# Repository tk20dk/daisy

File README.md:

# daisy
Sx1262 / Sx1268 usb gateway

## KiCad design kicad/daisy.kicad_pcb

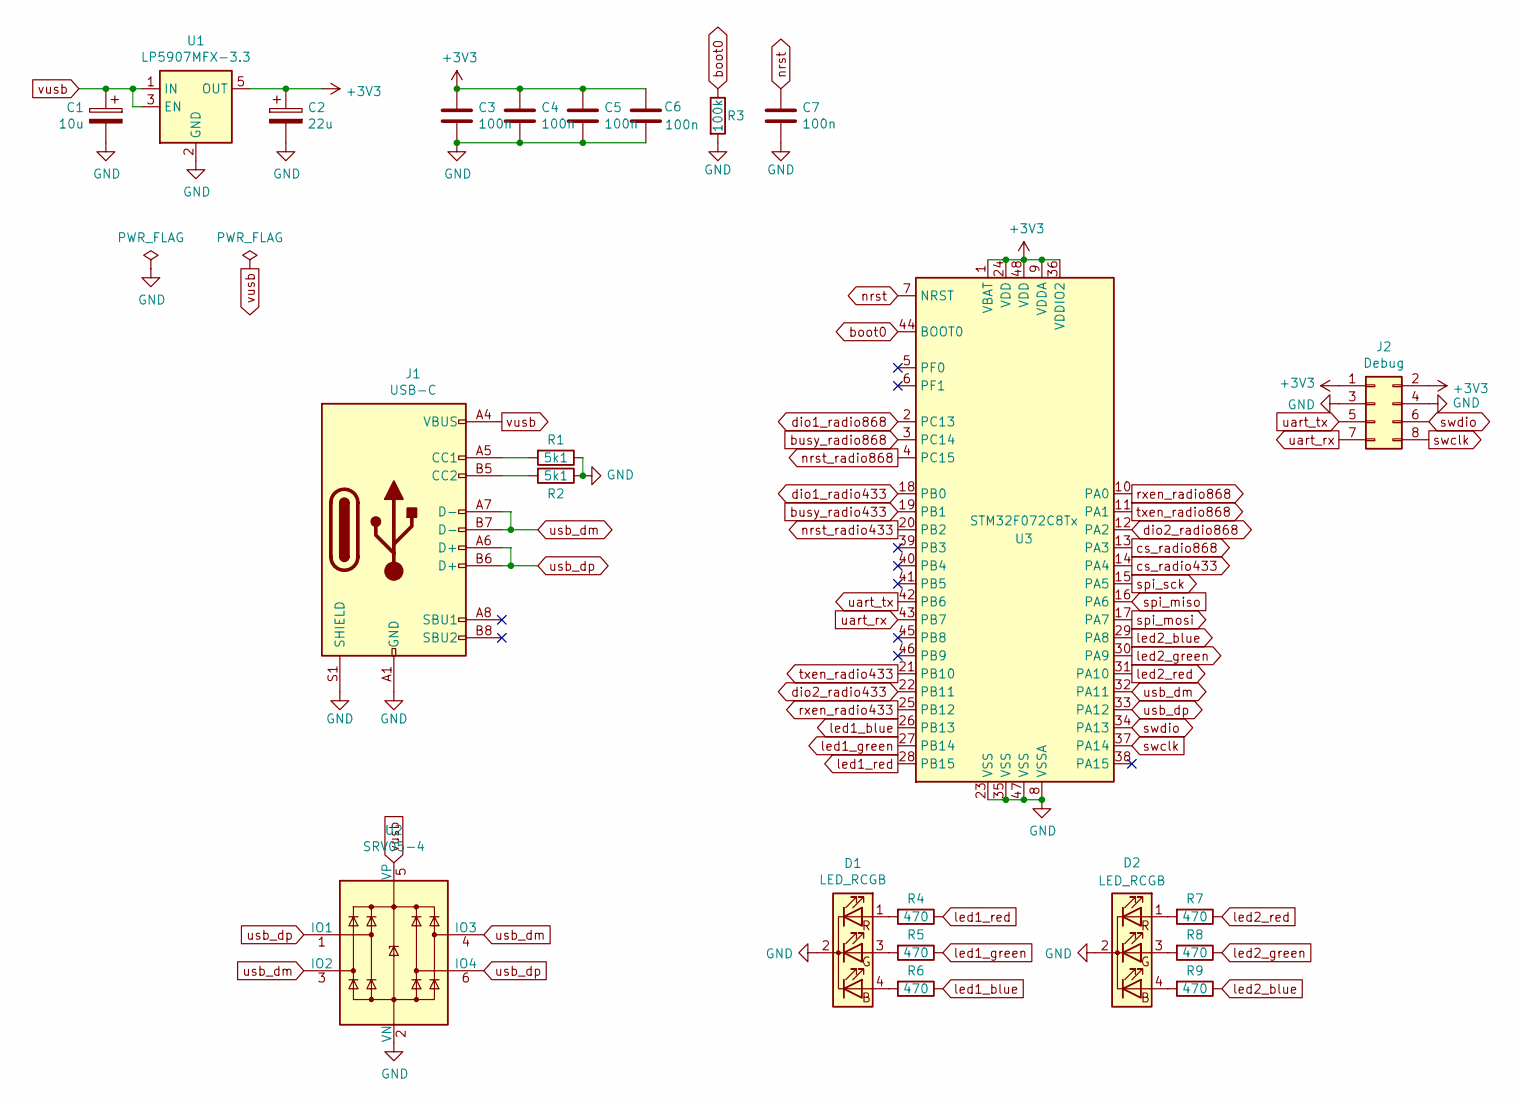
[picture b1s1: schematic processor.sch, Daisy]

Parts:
C1: 10u; CP_EIA-3528-12_Kemet-T
C2: 22u; CP_EIA-3528-12_Kemet-T
C3, C4, C5, C6, C7: 100n; C_0603_1608Metric
D1, D2: LED_RCGB; LED_D5.0mm-4
J1: USB-C; USB_C_Receptacle_HRO_TYPE-C-31-M-12
J2: Debug; PinHeader_2x04_P2.54mm_Vertical
R1, R2: 5k1; R_0603_1608Metric
R3: 100k; R_0603_1608Metric
R4, R5, R6, R7, R8, R9: 470; R_0603_1608Metric
U1: LP5907MFX-3.3; SOT-23-5
U2: SRV05-4; SOT-23-6
U3: STM32F072C8Tx; LQFP-48_7x7mm_P0.5mm

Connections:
GND: C1.2, C2.2, C3.2, C4.2, C5.2, C6.2, C7.2, D1.2 (K), D2.2 (K), J1.A1 (GND), J1.A12 (GND), J1.B1 (GND), J1.B12 (GND), J1.S1 (SHIELD), J2.3, J2.4, R1.1, R2.1, R3.2, U1.2 (GND), U2.2 (VN), U3.8 (VSSA), U3.23 (VSS), U3.35 (VSS), U3.47 (VSS); also elsewhere on the board
unnamed: D1.1 (RA), R4.2
unnamed: D1.3 (GA), R5.2
unnamed: D1.4 (BA), R6.2
unnamed: D2.1 (RA), R7.2
unnamed: D2.3 (GA), R8.2
unnamed: D2.4 (BA), R9.2
unnamed: J1.A5 (CC1), R1.2
unnamed: J1.B5 (CC2), R2.2
boot0: R3.1, U3.44 (BOOT0)
busy_radio433: U3.19 (PB1); also elsewhere on the board
busy_radio868: U3.3 (PC14); also elsewhere on the board
cs_radio433: U3.14 (PA4); also elsewhere on the board
cs_radio868: U3.13 (PA3); also elsewhere on the board
dio1_radio433: U3.18 (PB0); also elsewhere on the board
dio1_radio868: U3.2 (PC13); also elsewhere on the board
dio2_radio433: U3.22 (PB11); also elsewhere on the board
dio2_radio868: U3.12 (PA2); also elsewhere on the board
led1_blue: R6.1, U3.26 (PB13)
led1_green: R5.1, U3.27 (PB14)
led1_red: R4.1, U3.28 (PB15)
led2_blue: R9.1, U3.29 (PA8)
led2_green: R8.1, U3.30 (PA9)
led2_red: R7.1, U3.31 (PA10)
nrst: C7.1, U3.7 (NRST)
nrst_radio433: U3.20 (PB2); also elsewhere on the board
nrst_radio868: U3.4 (PC15); also elsewhere on the board
rxen_radio433: U3.25 (PB12); also elsewhere on the board
rxen_radio868: U3.10 (PA0); also elsewhere on the board
spi_miso: U3.16 (PA6); also elsewhere on the board
spi_mosi: U3.17 (PA7); also elsewhere on the board
spi_sck: U3.15 (PA5); also elsewhere on the board
swclk: J2.8, U3.37 (PA14)
swdio: J2.6, U3.34 (PA13)
txen_radio433: U3.21 (PB10); also elsewhere on the board
txen_radio868: U3.11 (PA1); also elsewhere on the board
uart_rx: J2.7, U3.43 (PB7)
uart_tx: J2.5, U3.42 (PB6)
usb_dm: J1.A7 (D-), J1.B7 (D-), U2.3 (IO2), U2.4 (IO3), U3.32 (PA11)
usb_dp: J1.A6 (D+), J1.B6 (D+), U2.1 (IO1), U2.6 (IO4), U3.33 (PA12)
vusb: C1.1, J1.A4 (VBUS), J1.A9 (VBUS), J1.B4 (VBUS), J1.B9 (VBUS), U1.1 (IN), U1.3 (EN), U2.5 (VP)

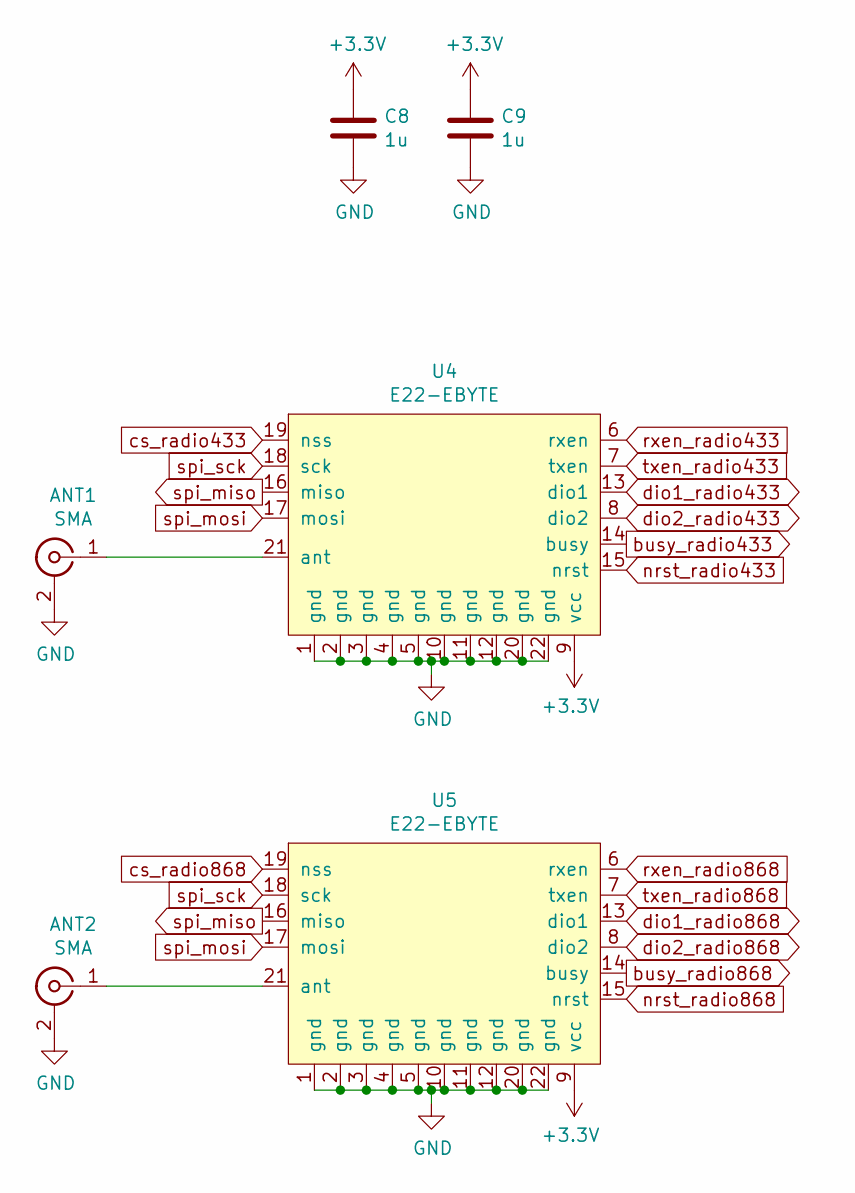
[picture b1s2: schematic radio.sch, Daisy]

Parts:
ANT1, ANT2: SMA; SMA_Molex_73251-2200_Horizontal
C8, C9: 1u; C_0805_2012Metric
U4, U5: E22-EBYTE

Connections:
GND: ANT1.2 (Ext), ANT2.2 (Ext), C8.2, C9.2, U4.1 (gnd), U4.2 (gnd), U4.3 (gnd), U4.4 (gnd), U4.5 (gnd), U4.10 (gnd), U4.11 (gnd), U4.12 (gnd), U4.20 (gnd), U4.22 (gnd), U5.1 (gnd), U5.2 (gnd), U5.3 (gnd), U5.4 (gnd), U5.5 (gnd), U5.10 (gnd), U5.11 (gnd), U5.12 (gnd), U5.20 (gnd), U5.22 (gnd); also elsewhere on the board
unnamed: ANT1.1 (In), U4.21 (ant)
unnamed: ANT2.1 (In), U5.21 (ant)
busy_radio433: U4.14 (busy); also elsewhere on the board
busy_radio868: U5.14 (busy); also elsewhere on the board
cs_radio433: U4.19 (nss); also elsewhere on the board
cs_radio868: U5.19 (nss); also elsewhere on the board
dio1_radio433: U4.13 (dio1); also elsewhere on the board
dio1_radio868: U5.13 (dio1); also elsewhere on the board
dio2_radio433: U4.8 (dio2); also elsewhere on the board
dio2_radio868: U5.8 (dio2); also elsewhere on the board
nrst_radio433: U4.15 (nrst); also elsewhere on the board
nrst_radio868: U5.15 (nrst); also elsewhere on the board
rxen_radio433: U4.6 (rxen); also elsewhere on the board
rxen_radio868: U5.6 (rxen); also elsewhere on the board
spi_miso: U4.16 (miso), U5.16 (miso); also elsewhere on the board
spi_mosi: U4.17 (mosi), U5.17 (mosi); also elsewhere on the board
spi_sck: U4.18 (sck), U5.18 (sck); also elsewhere on the board
txen_radio433: U4.7 (txen); also elsewhere on the board
txen_radio868: U5.7 (txen); also elsewhere on the board

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
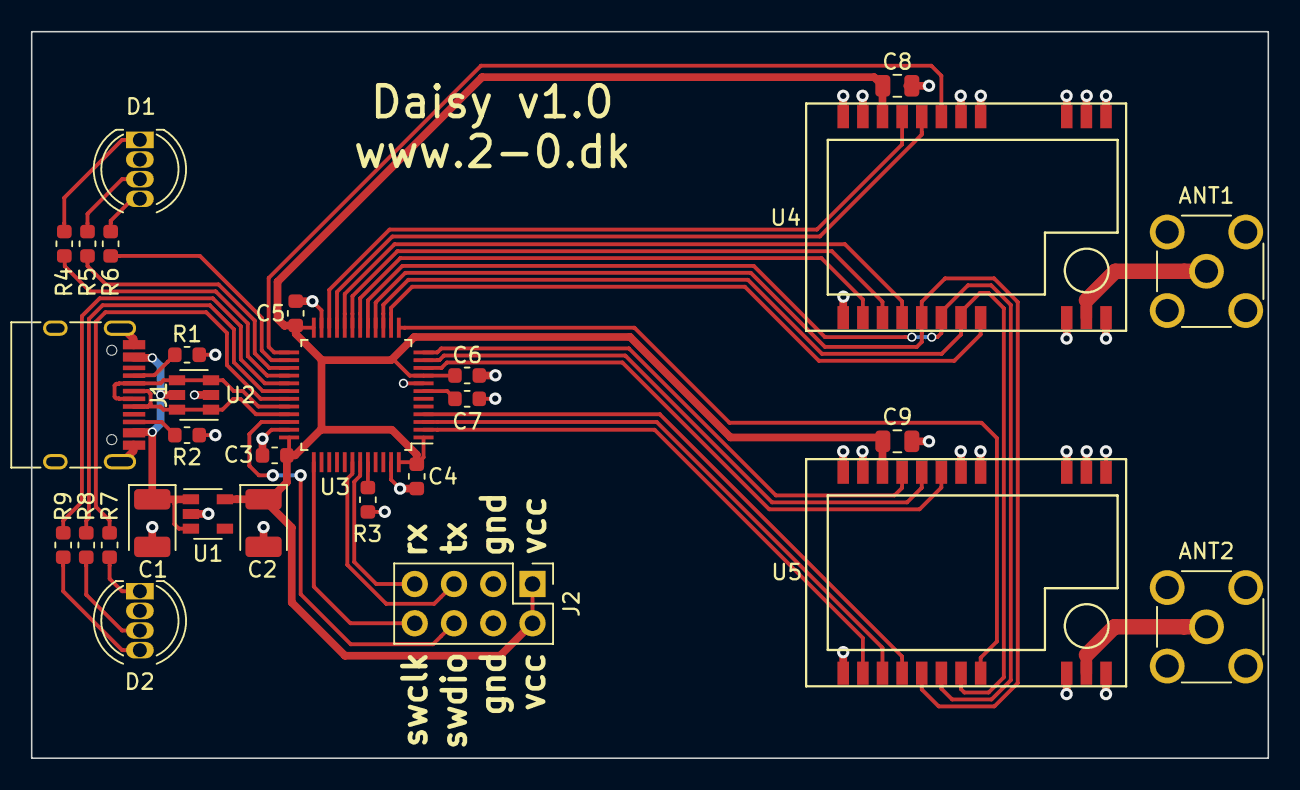
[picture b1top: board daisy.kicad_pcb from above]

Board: 2 copper layers, 80.0 x 47.0 mm, 29 parts (0 on the bottom side), 44 nets.

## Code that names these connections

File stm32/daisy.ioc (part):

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Mcu.Name=STM32F072C(8-B)Tx
Mcu.Package=LQFP48
Mcu.UserName=STM32F072C8Tx
PA0.GPIOParameters=GPIO_Label
PA0.GPIO_Label=RXEN_RADIO868
PA0.Signal=GPIO_Output
PA1.GPIOParameters=GPIO_Label
PA1.GPIO_Label=TXEN_RADIO868
PA1.Signal=GPIO_Output
PA10.GPIOParameters=GPIO_Label
PA10.GPIO_Label=LED2_RED
PA10.Signal=GPIO_Output
PA11.Mode=Device
PA11.Signal=USB_DM
PA12.Mode=Device
PA12.Signal=USB_DP
PA13.Mode=Serial_Wire
PA13.Signal=SYS_SWDIO
PA14.Mode=Serial_Wire
PA14.Signal=SYS_SWCLK
PA2.GPIOParameters=GPIO_PuPd,GPIO_Label
PA2.GPIO_Label=DIO2_RADIO868
PA2.GPIO_PuPd=GPIO_PULLUP
PA2.Signal=GPIO_Input
PA3.GPIOParameters=PinState,GPIO_Label
PA3.GPIO_Label=NSS_RADIO868
PA3.PinState=GPIO_PIN_SET
PA3.Signal=GPIO_Output
PA4.GPIOParameters=PinState,GPIO_Label
PA4.GPIO_Label=NSS_RADIO433
PA4.PinState=GPIO_PIN_SET
PA4.Signal=GPIO_Output
PA5.Mode=Full_Duplex_Master
PA5.Signal=SPI1_SCK
PA6.GPIOParameters=GPIO_PuPd
PA6.GPIO_PuPd=GPIO_PULLUP
PA6.Mode=Full_Duplex_Master
PA6.Signal=SPI1_MISO
PA7.Mode=Full_Duplex_Master
PA7.Signal=SPI1_MOSI
PA8.GPIOParameters=GPIO_Label
PA8.GPIO_Label=LED2_BLUE
PA8.Signal=GPIO_Output
PA9.GPIOParameters=GPIO_Label
PA9.GPIO_Label=LED2_GREEN
PA9.Signal=GPIO_Output
PB0.GPIOParameters=GPIO_PuPd,GPIO_Label,GPIO_ModeDefaultEXTI
PB0.GPIO_Label=DIO1_RADIO433
PB0.GPIO_ModeDefaultEXTI=GPIO_MODE_IT_RISING
PB0.GPIO_PuPd=GPIO_PULLDOWN
PB0.Signal=GPXTI0
PB1.GPIOParameters=GPIO_Label
PB1.GPIO_Label=BUSY_RADIO433
PB1.Signal=GPIO_Input
PB10.GPIOParameters=GPIO_Label
PB10.GPIO_Label=TXEN_RADIO433
PB10.Signal=GPIO_Output
PB11.GPIOParameters=GPIO_PuPd,GPIO_Label
PB11.GPIO_Label=DIO2_RADIO433
PB11.GPIO_PuPd=GPIO_PULLUP
PB11.Signal=GPIO_Input
PB12.GPIOParameters=GPIO_Label
PB12.GPIO_Label=RXEN_RADIO433
PB12.Signal=GPIO_Output
PB13.GPIOParameters=GPIO_Label
PB13.GPIO_Label=LED1_BLUE
PB13.Signal=GPIO_Output
PB14.GPIOParameters=GPIO_Label
PB14.GPIO_Label=LED1_GREEN
PB14.Signal=GPIO_Output
PB15.GPIOParameters=GPIO_Label
PB15.GPIO_Label=LED1_RED
PB15.Signal=GPIO_Output
PB2.GPIOParameters=GPIO_Label
PB2.GPIO_Label=NRST_RADIO433
PB2.Signal=GPIO_Output
PB6.Mode=Asynchronous
PB6.Signal=USART1_TX
PB7.GPIOParameters=GPIO_PuPd
PB7.GPIO_PuPd=GPIO_PULLUP
PB7.Mode=Asynchronous
PB7.Signal=USART1_RX
PC13.GPIOParameters=GPIO_PuPd,GPIO_Label,GPIO_ModeDefaultEXTI
PC13.GPIO_Label=DIO1_RADIO868
PC13.GPIO_ModeDefaultEXTI=GPIO_MODE_IT_RISING
PC13.GPIO_PuPd=GPIO_PULLDOWN
PC13.Signal=GPXTI13
PC14-OSC32_IN.GPIOParameters=GPIO_Label
PC14-OSC32_IN.GPIO_Label=BUSY_RADIO868
PC14-OSC32_IN.Signal=GPIO_Input
PC15-OSC32_OUT.GPIOParameters=GPIO_Label
PC15-OSC32_OUT.GPIO_Label=NRST_RADIO868
PC15-OSC32_OUT.Signal=GPIO_Output
RCC.SYSCLKFreq_VALUE=48000000
RCC.SYSCLKSource=RCC_SYSCLKSOURCE_HSI48
board=custom

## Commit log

2020-11-19 created initial kicad and stm32 projects
2020-11-28 added sbus server
2020-11-30 updated sbus server to send with 10ms interval
